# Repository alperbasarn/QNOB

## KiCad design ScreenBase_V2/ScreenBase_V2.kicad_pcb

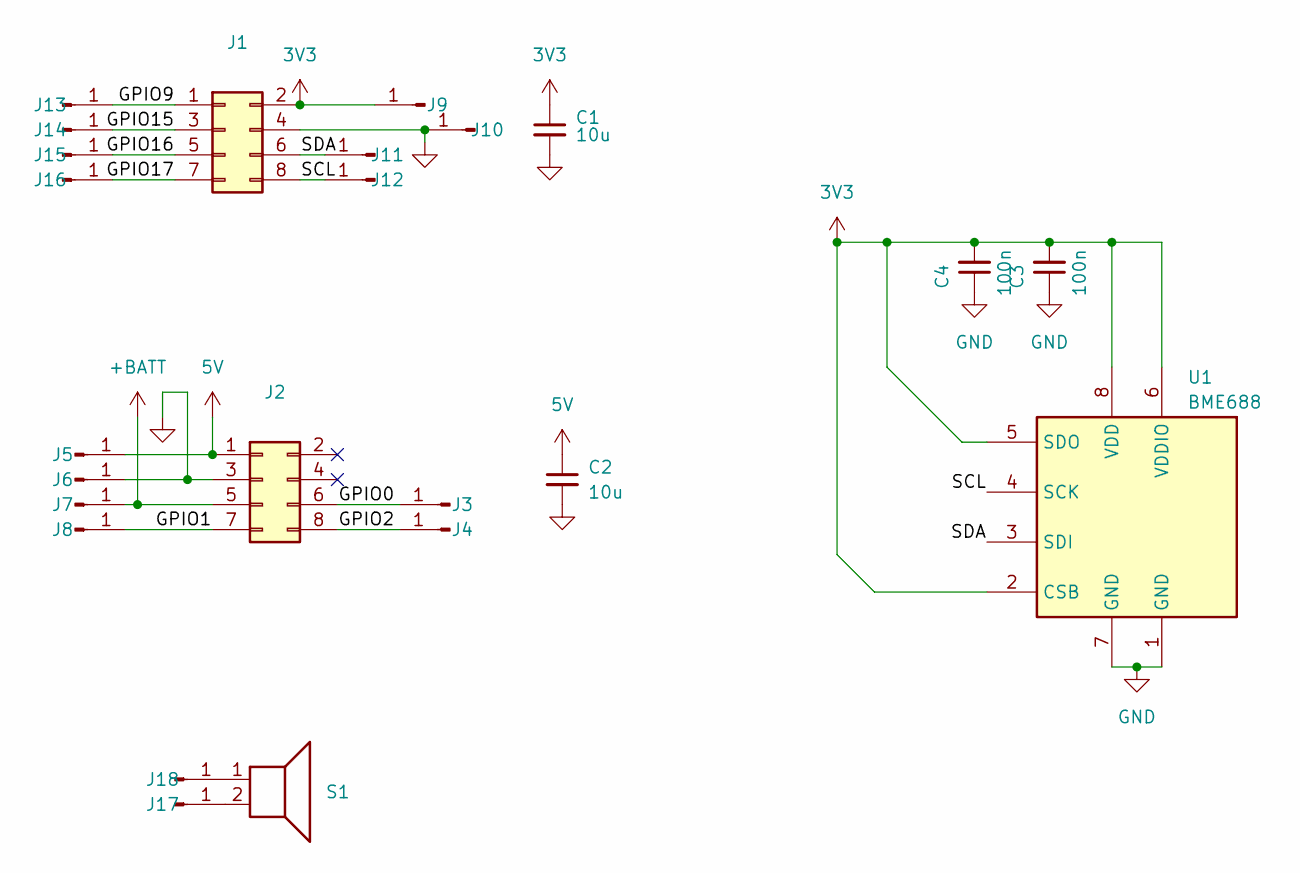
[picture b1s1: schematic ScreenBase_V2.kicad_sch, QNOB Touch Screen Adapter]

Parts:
C1, C2: 10u; C_0805_2012Metric_Pad1.18x1.45mm_HandSolder
C3, C4: 100n; C_0805_2012Metric_Pad1.18x1.45mm_HandSolder
J1, J2: Connector_PinHeader_2.54mm:PinHeader_2x04_P2.54mm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; PinHeader_2x04_P2.54mm_Vertical
J3, J4, J5, J6, J7, J8, J9, J10, J11, J12, J13, J14, J15, J16, J17, J18: Conn_01x01_Pin; SolderWirePad_1x01_SMD_1x2mm
S1: Speaker; speaker_custom
U1: BME688; Bosch_LGA-8_3x3mm_P0.8mm_ClockwisePinNumbering

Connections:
3V3: C1.1, C3.2, C4.2, J1.2, J9.1, U1.2 (CSB), U1.5 (SDO), U1.6 (VDDIO), U1.8 (VDD)
5V: C2.1, J2.1, J5.1
+BATT: J2.5, J7.1
/GPIO0: J2.6, J3.1
/GPIO1: J2.7, J8.1
/GPIO2: J2.8, J4.1
/GPIO9: J1.1, J13.1
/GPIO15: J1.3, J14.1
/GPIO16: J1.5, J15.1
/GPIO17: J1.7, J16.1
/SCL: J1.8, J12.1, U1.4 (SCK)
/SDA: J1.6, J11.1, U1.3 (SDI)
GND: C1.2, C2.2, C3.1, C4.1, J1.4, J2.3, J6.1, J10.1, U1.1 (GND), U1.7 (GND)
unnamed: J17.1, S1.2
unnamed: J18.1, S1.1

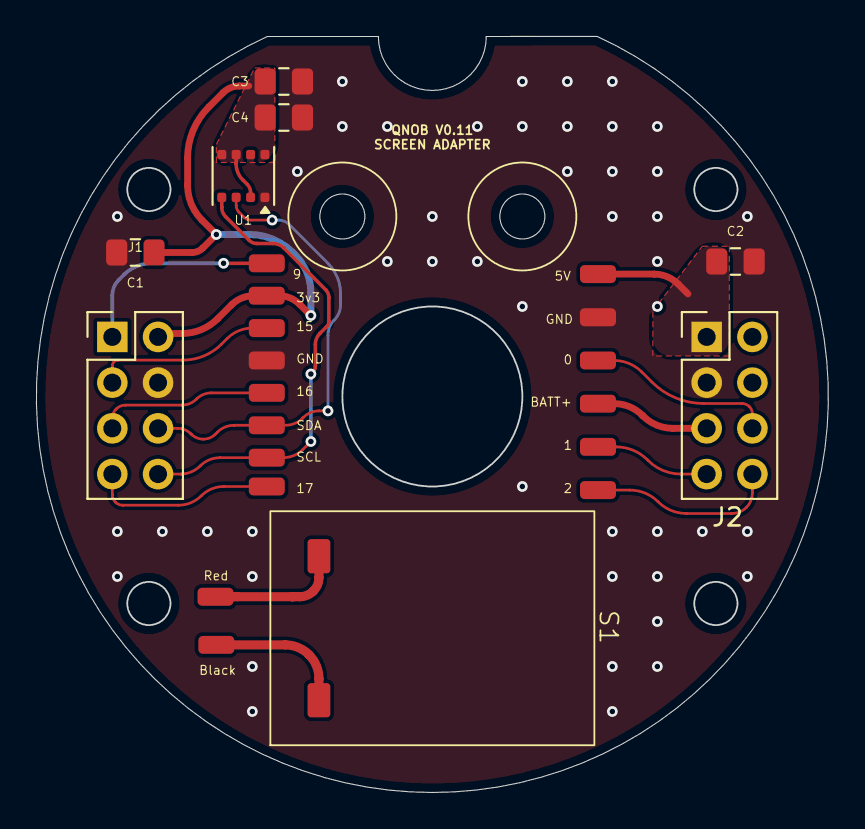
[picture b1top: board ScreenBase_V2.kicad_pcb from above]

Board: 2 copper layers, 44.0 x 42.0 mm, 24 parts (0 on the bottom side), 15 nets.

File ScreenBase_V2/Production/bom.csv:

Designator,Footprint,Quantity,Value,LCSC Part #
"C1, C2",0805,2,10u,
"C3, C4",0805,2,100n,
"J1, J2",PinHeader_2x04_P2.54mm_Vertical,2,Connector_PinHeader_2.54mm:PinHeader_2x04_P2.54mm_Vertical_SMD,
"J10, J11, J12, J13, J14, J15, J16, J17, J18, J3, J4, J5, J6, J7, J8, J9",SolderWirePad_1x01_SMD_1x2mm,16,Conn_01x01_Pin,
S1,speaker_custom,1,Speaker,
U1,Bosch_LGA-8_3x3mm_P0.8mm_ClockwisePinNumbering,1,BME688,

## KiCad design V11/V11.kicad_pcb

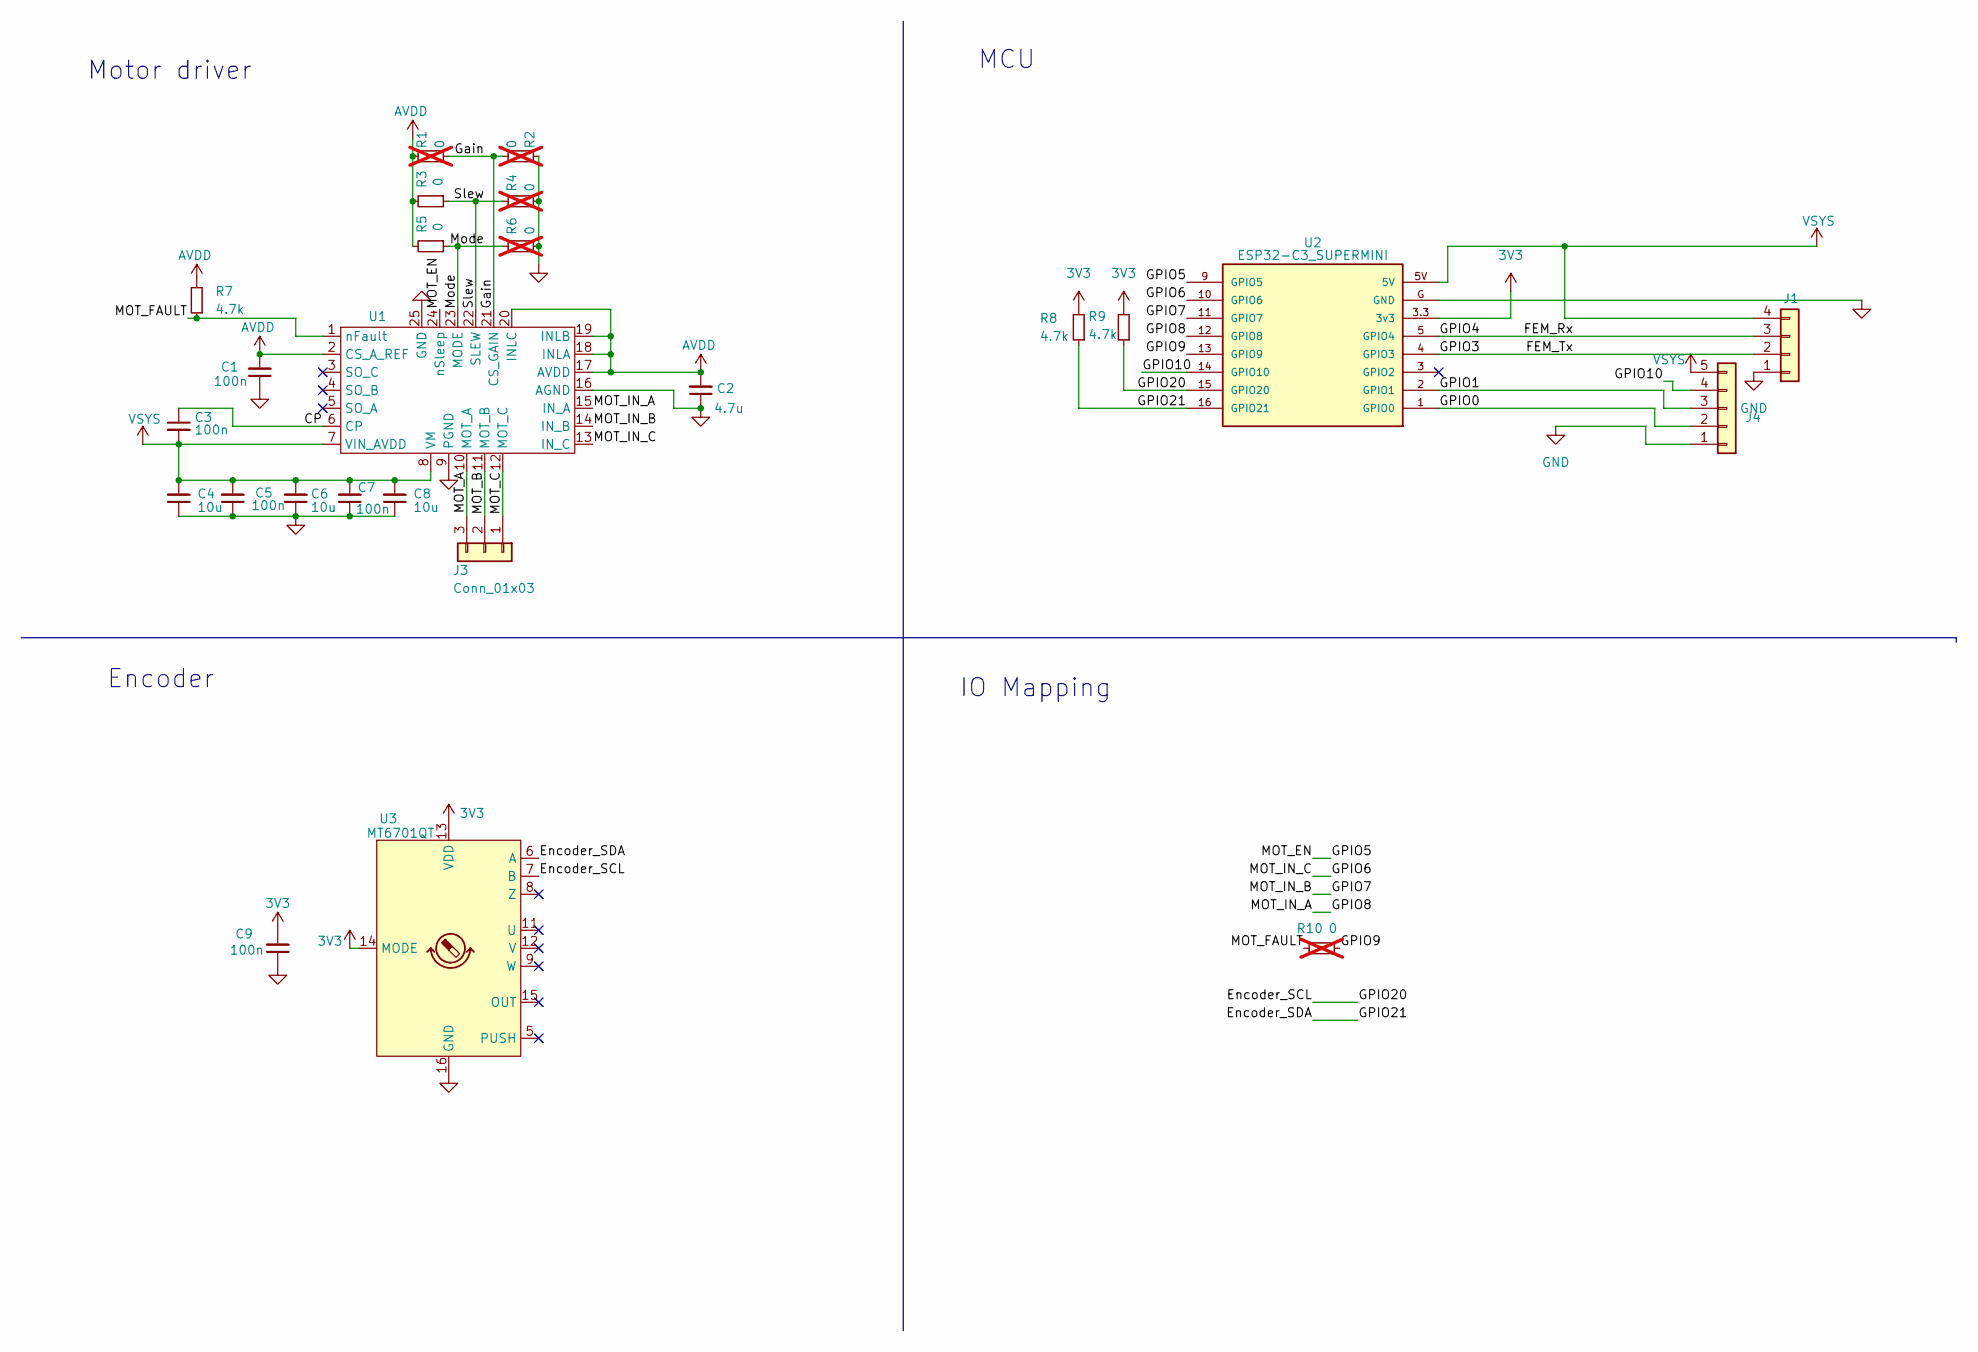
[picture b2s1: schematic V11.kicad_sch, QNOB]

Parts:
C1, C3, C5, C7, C9: 100n; C_0603_1608Metric_Pad1.08x0.95mm_HandSolder
C2: 4.7u; C_0603_1608Metric_Pad1.08x0.95mm_HandSolder
C4, C6, C8: 10u; C_0603_1608Metric_Pad1.08x0.95mm_HandSolder
J1: Conn_01x04; Molex_PicoBlade_53048-0410_1x04_P1.25mm_Horizontal
J3: Conn_01x03; Molex_PicoBlade_53048-0310_1x03_P1.25mm_Horizontal
J4: Conn_01x05; PinHeader_1x05_P2.54mm_Vertical
R1, R2, R4, R6, R10: 0; R_0603_1608Metric_Pad0.98x0.95mm_HandSolder; not fitted
R3, R5: 0; R_0603_1608Metric_Pad0.98x0.95mm_HandSolder
R7, R8, R9: 4.7k; R_0603_1608Metric_Pad0.98x0.95mm_HandSolder
U1: IC_DRV8311HRRWR
U2: ESP32-C3_SUPERMINI; MODULE_ESP32-C3_SUPERMINI
U3: MT6701QT; QFN-16-1EP_3x3mm_P0.5mm_EP1.7x1.7mm

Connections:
3V3: C9.2, R8.2, R9.2, U2.3.3 (3v3), U3.13 (VDD), U3.14 (MODE); also elsewhere on the board
/CP: C3.1, U1.6 (CP)
/CS_A: U1.5 (SO_A)
/CS_B: U1.4 (SO_B)
/CS_C: U1.3 (SO_C)
/Encoder_SCL: R9.1, U2.15 (GPIO20), U3.7 (B)
/Encoder_SDA: R8.1, U2.16 (GPIO21), U3.6 (A)
/FEM_Rx: J1.3, U2.5 (GPIO4)
/FEM_Tx: J1.2, U2.4 (GPIO3)
/GPIO0: J4.2, U2.1 (GPIO0)
/GPIO1: J4.3, U2.2 (GPIO1)
/GPIO5: U1.24 (nSleep), U2.9 (GPIO5)
/GPIO6: U1.13 (IN_C), U2.10 (GPIO6)
/GPIO7: U1.14 (IN_B), U2.11 (GPIO7)
/GPIO8: U1.15 (IN_A), U2.12 (GPIO8)
/GPIO9: R10.1, U2.13 (GPIO9)
/GPIO10: J4.4, U2.14 (GPIO10)
/Gain: R1.1, R2.1, U1.21 (CS_GAIN)
/MOT_A: J3.3, U1.10 (MOT_A)
/MOT_B: J3.2, U1.11 (MOT_B)
/MOT_C: J3.1, U1.12 (MOT_C)
/MOT_FAULT: R7.1, R10.2, U1.1 (nFault)
/Mode: R5.1, R6.2, U1.23 (MODE)
/Slew: R3.1, R4.2, U1.22 (SLEW)
AVDD: C1.2, C2.2, R1.2, R3.2, R5.2, R7.2, U1.2 (CS_A_REF), U1.17 (AVDD), U1.18 (INLA), U1.19 (INLB), U1.20 (INLC)
GND: C1.1, C2.1, C4.1, C5.1, C6.1, C7.1, C8.1, C9.1, J1.1, J4.1, R2.2, R4.1, R6.1, U1.9 (PGND), U1.16 (AGND), U1.25 (GND), U2.G (GND), U3.16 (GND), U3.17 (GND); also elsewhere on the board
VSYS: C3.2, C4.2, C5.2, C6.2, C7.2, C8.2, J1.4, J4.5, U1.7 (VIN_AVDD), U1.8 (VM), U2.5V; also elsewhere on the board

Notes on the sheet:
Encoder
Motor driver
IO Mapping
MCU

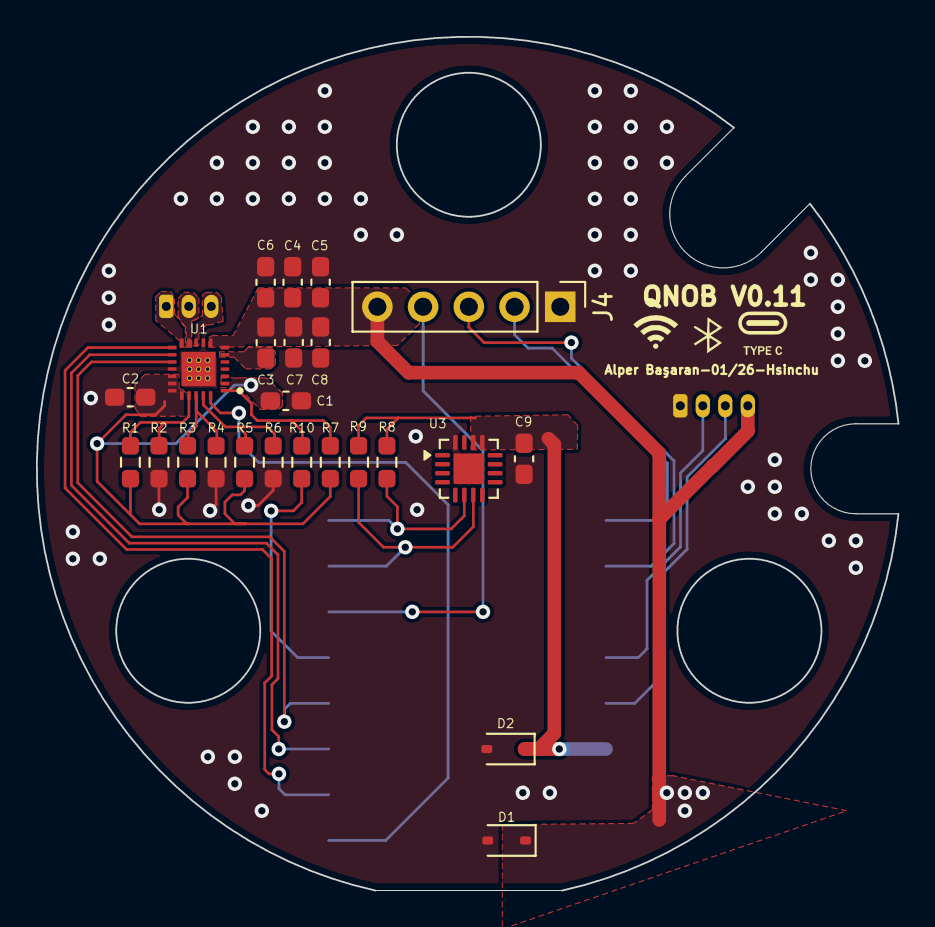
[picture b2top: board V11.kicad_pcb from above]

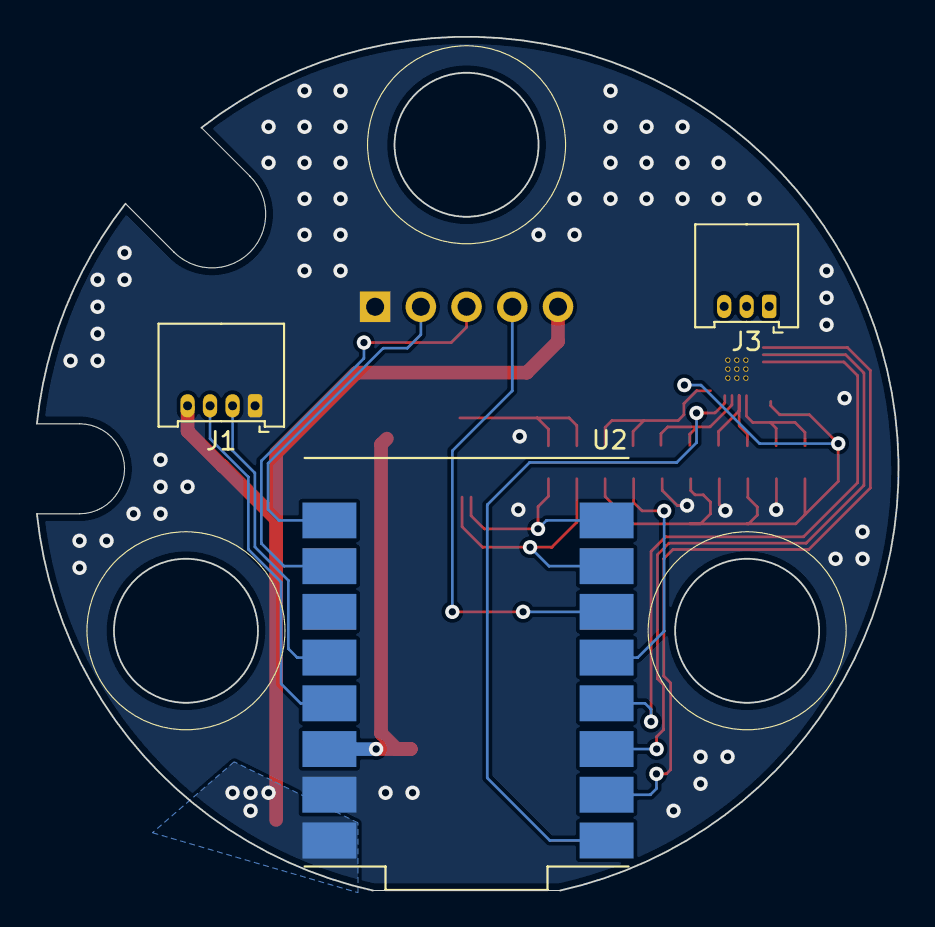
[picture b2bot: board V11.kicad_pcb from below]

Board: 2 copper layers, 47.9 x 47.4 mm, 27 parts (3 on the bottom side), 24 nets.

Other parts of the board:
D1, D2: ESD5Zxx; D_SOD-323

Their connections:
3V3: D2.1 (K); also elsewhere on the board
GND: D1.2 (A), D2.2 (A); also elsewhere on the board
VSYS: D1.1 (K); also elsewhere on the board

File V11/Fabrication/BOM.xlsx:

Comment | Designator | Footprint | JLCPCB Part #（optional）
100n | C1,C3,C5,C7,C9 | 603 | C14663
4.7u | C2 | 603 | C19666
10u | C4,C6,C8 | 603 | C96446
0 | R3,R5 | 603 | C21189
4.7k | R7,R8,R9 | 603 | C23162
DRV8311HRWR | U1 | WQFN-24(3x3) | C5218862
MT6701QT | U3 | QFN-16-1EP_3x3mm_P0.5mm_EP1.7x1.7mm | C2913974

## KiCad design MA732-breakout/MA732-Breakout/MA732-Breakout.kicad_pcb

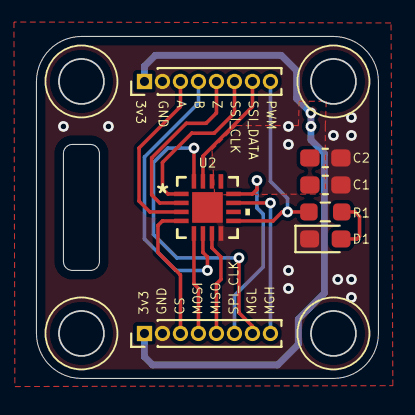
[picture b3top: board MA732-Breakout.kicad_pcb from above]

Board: 2 copper layers, 19.0 x 19.0 mm, 7 parts (0 on the bottom side), 15 nets.

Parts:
C1: 10u; C_0603_1608Metric_Pad1.08x0.95mm_HandSolder
C2: 100n; C_0603_1608Metric_Pad1.08x0.95mm_HandSolder
D1: white; LED_0603_1608Metric_Pad1.05x0.95mm_HandSolder
J1, J2: Conn_01x08_Pin; PinHeader_1x08_P1.00mm_Vertical
R1: 1k; R_0603_1608Metric_Pad0.98x0.95mm_HandSolder
U2: MA732GQ-Z; QFN-16_MA732

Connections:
3v3: C1.2, C2.2, J1.1, J2.1, U2.13 (VDD)
/A: J2.5, U2.2 (A)
/B: J2.4, U2.6 (B)
/CS: J1.4, U2.5 (CS)
/MGH: J1.7, U2.16 (MGH)
/MGL: J1.8, U2.11 (MGL)
/MISO: J1.5, U2.7 (MISO)
/MOSI: J1.3, U2.4 (MOSI)
/PWM: J2.8, R1.1, U2.9 (PWM)
/SPI_CLK: J1.6, U2.12 (SCLK)
/SSI_CLK: J2.7, U2.15 (SSCK)
/SSI_Data: J2.6, U2.1 (SSD)
/Z: J2.3, U2.3 (Z)
GND: C1.1, C2.1, D1.1 (K), J1.2, J2.2, U2.8 (GND), U2.17 (PAD)
unnamed: D1.2 (A), R1.2

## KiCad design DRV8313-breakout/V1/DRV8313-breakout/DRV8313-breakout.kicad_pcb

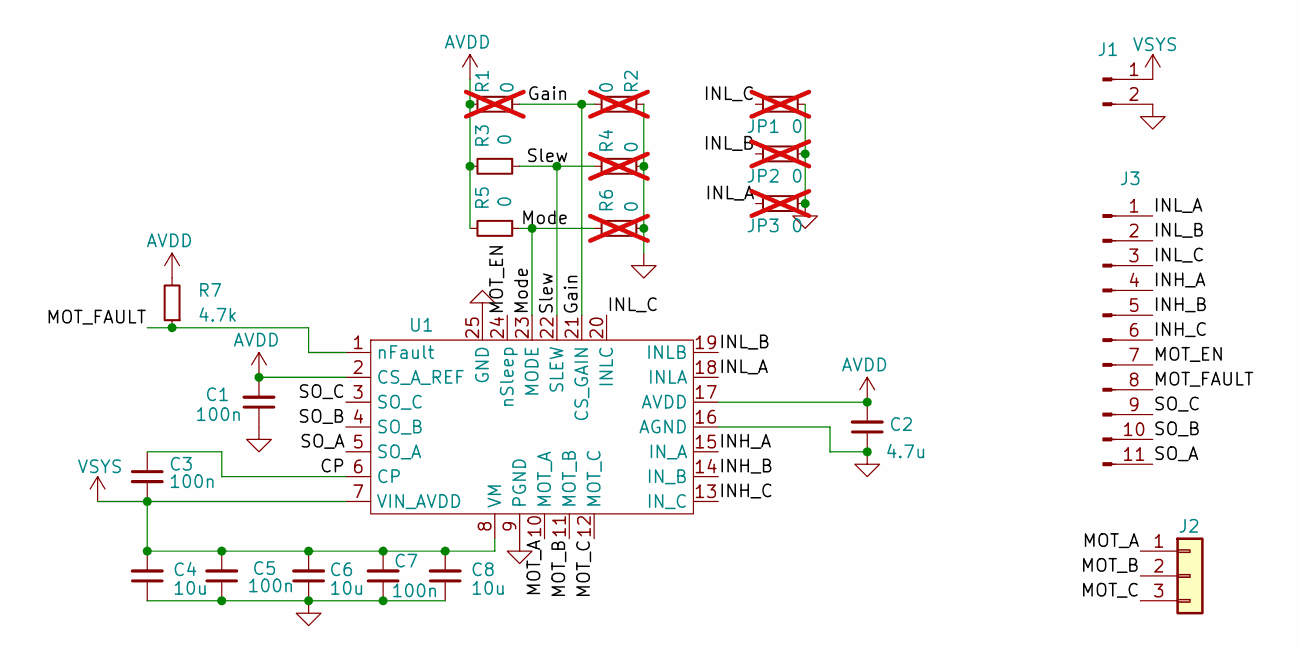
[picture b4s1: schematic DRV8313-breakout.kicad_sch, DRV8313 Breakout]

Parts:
C1, C3, C5, C7: 100n; C_0603_1608Metric_Pad1.08x0.95mm_HandSolder
C2: 4.7u; C_0603_1608Metric_Pad1.08x0.95mm_HandSolder
C4, C6, C8: 10u; C_0603_1608Metric_Pad1.08x0.95mm_HandSolder
J1: Conn_01x02_Pin; Molex_PicoBlade_53048-0210_1x02_P1.25mm_Horizontal
J2: Conn_01x03; Molex_PicoBlade_53048-0310_1x03_P1.25mm_Horizontal
J3: Conn_01x11_Pin; Molex_PicoBlade_53048-1110_1x11_P1.25mm_Horizontal
JP1, JP2, JP3: 0; R_0603_1608Metric_Pad0.98x0.95mm_HandSolder; not fitted
R1, R2, R4, R6: 0; R_0603_1608Metric_Pad0.98x0.95mm_HandSolder; not fitted
R3, R5: 0; R_0603_1608Metric_Pad0.98x0.95mm_HandSolder
R7: 4.7k; R_0603_1608Metric_Pad0.98x0.95mm_HandSolder
U1: IC_DRV8311HRRWR

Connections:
/CP: C3.1, U1.6 (CP)
/Gain: R1.1, R2.1, U1.21 (CS_GAIN)
/INH_A: J3.4, U1.15 (IN_A)
/INH_B: J3.5, U1.14 (IN_B)
/INH_C: J3.6, U1.13 (IN_C)
/INL_A: J3.1, JP3.1, U1.18 (INLA)
/INL_B: J3.2, JP2.1, U1.19 (INLB)
/INL_C: J3.3, JP1.1, U1.20 (INLC)
/MOT_A: J2.1, U1.10 (MOT_A)
/MOT_B: J2.2, U1.11 (MOT_B)
/MOT_C: J2.3, U1.12 (MOT_C)
/MOT_EN: J3.7, U1.24 (nSleep)
/MOT_FAULT: J3.8, R7.1, U1.1 (nFault)
/Mode: R5.1, R6.2, U1.23 (MODE)
/SO_A: J3.11, U1.5 (SO_A)
/SO_B: J3.10, U1.4 (SO_B)
/SO_C: J3.9, U1.3 (SO_C)
/Slew: R3.1, R4.2, U1.22 (SLEW)
AVDD: C1.2, C2.2, R1.2, R3.2, R5.2, R7.2, U1.2 (CS_A_REF), U1.17 (AVDD)
GND: C1.1, C2.1, C4.1, C5.1, C6.1, C7.1, C8.1, J1.2, JP1.2, JP2.2, JP3.2, R2.2, R4.1, R6.1, U1.9 (PGND), U1.16 (AGND), U1.25 (GND)
VSYS: C3.2, C4.2, C5.2, C6.2, C7.2, C8.2, J1.1, U1.7 (VIN_AVDD), U1.8 (VM)

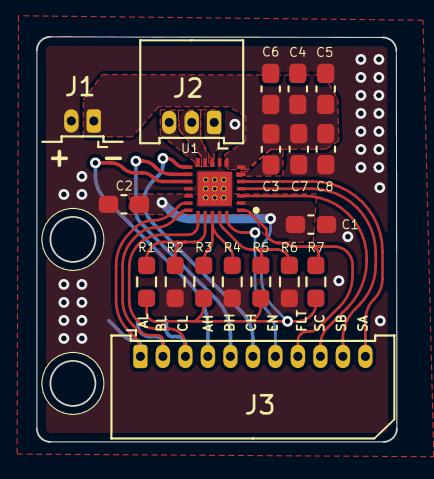
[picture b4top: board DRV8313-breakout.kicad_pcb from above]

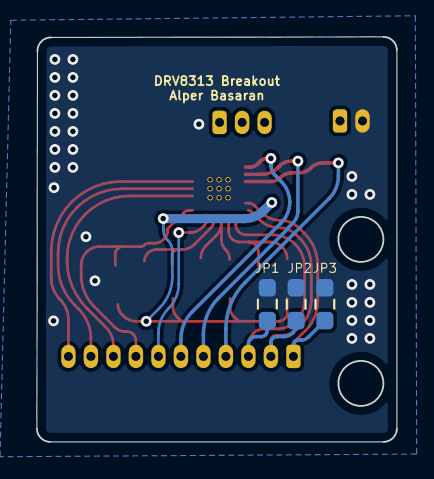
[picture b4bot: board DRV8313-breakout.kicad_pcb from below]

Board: 2 copper layers, 20.0 x 22.5 mm, 22 parts (3 on the bottom side), 21 nets.

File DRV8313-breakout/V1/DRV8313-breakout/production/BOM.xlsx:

Comment | Designator | Footprint | JLCPCB Part #（optional）
100n | C1,C3,C5,C7,C9 | 603 | C14663
4.7u | C2 | 603 | C19666
10u | C4,C6,C8 | 603 | C96446
0 | R3,R5 | 603 | C21189
4.7k | R7 | 603 | C23162
DRV8311HRWR | U1 | WQFN-24(3x3) | C5218862

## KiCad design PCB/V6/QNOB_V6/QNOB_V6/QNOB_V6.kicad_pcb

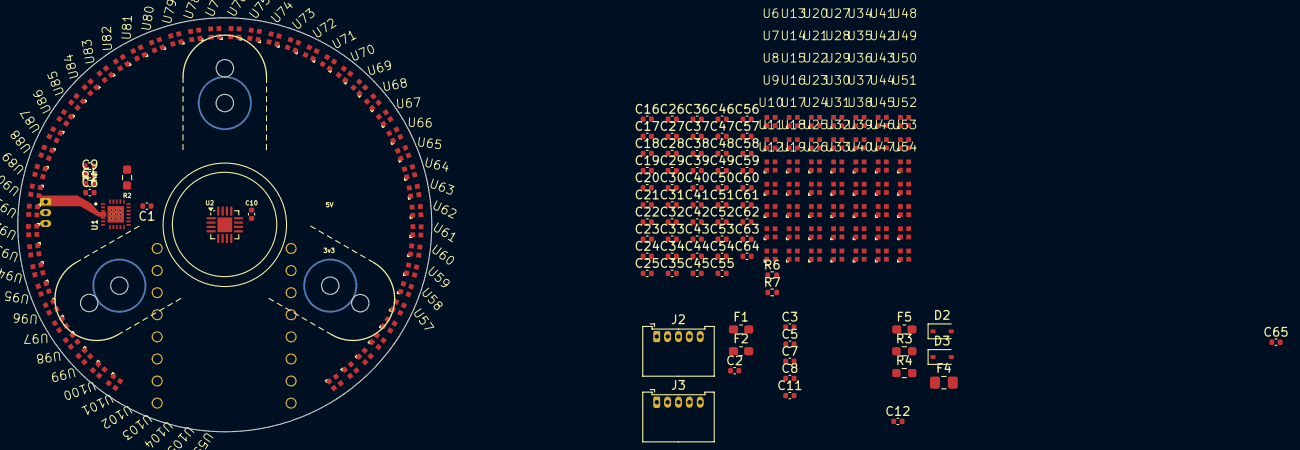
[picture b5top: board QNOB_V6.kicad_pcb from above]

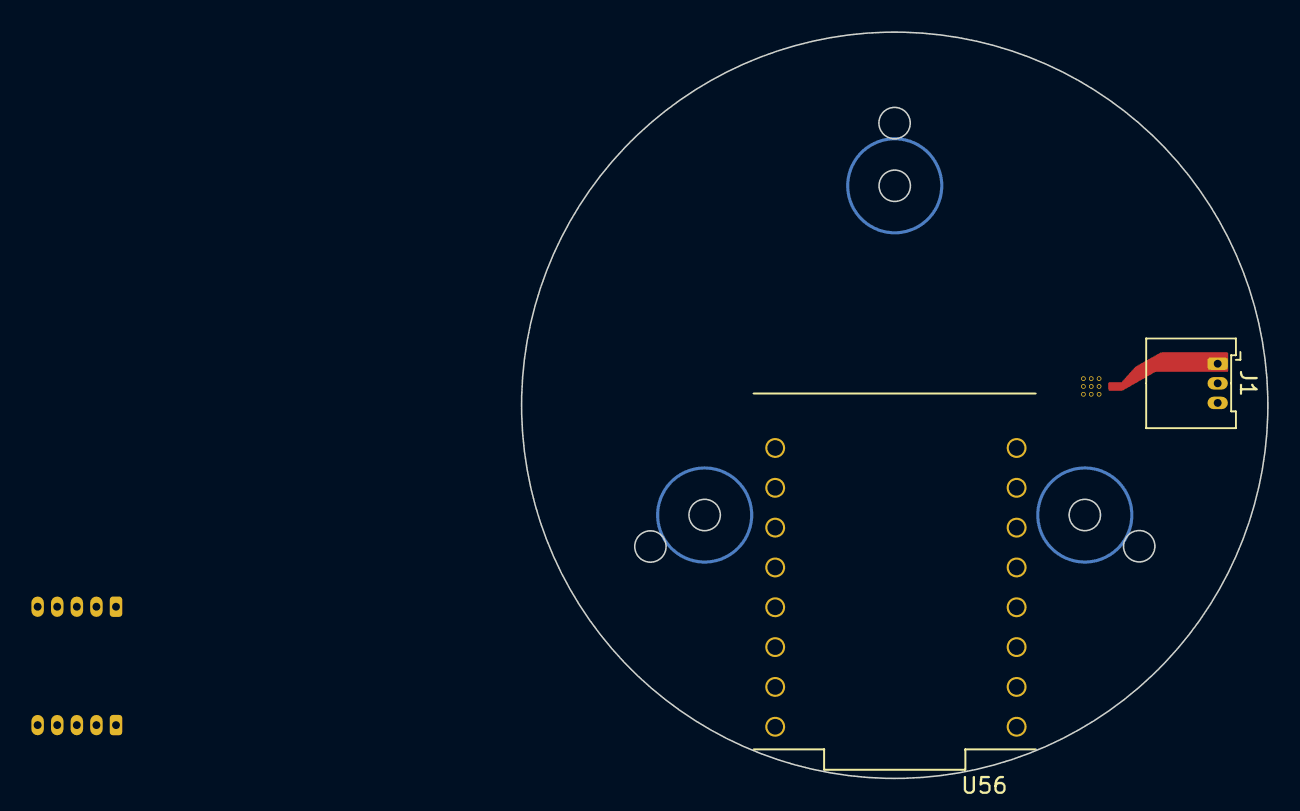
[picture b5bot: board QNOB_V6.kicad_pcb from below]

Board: 2 copper layers, 47.6 x 47.6 mm, 179 parts (2 on the bottom side), 70 nets, no tracks yet.

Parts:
C1, C2, C4, C5, C6, C7: 10u; C_0402_1005Metric
C3, C8, C9, C10, C12: 100n; C_0402_1005Metric
C11: 4.7u; C_0402_1005Metric
C16, C17, C18, C19, C20, C21, C22, C23, C24, C25, C26, C27, C28, C29, C30, C31, C32, C33, C34, C35, C36, C37, C38, C39, C40, C41, C42, C43, C44, C45, C46, C47, C48, C49, C50, C51, C52, C53, C54, C55, C56, C57, C58, C59, C60, C61, C62, C63, C64, C65: 100n 10V; C_0402_1005Metric
D2, D3: ESD5Zxx; D_SOD-323
F1, F2, F5: 500m; Fuse_0603_1608Metric_Pad1.05x0.95mm_HandSolder
F4: 1A; Fuse_0805_2012Metric_Pad1.15x1.40mm_HandSolder
J1: Conn_01x03; Molex_PicoBlade_53048-0310_1x03_P1.25mm_Horizontal
J2, J3: Conn_01x05; Molex_PicoBlade_53048-0510_1x05_P1.25mm_Horizontal
R1: 4.7k; R_0402_1005Metric
R2: 0; R_0603_1608Metric_Pad0.98x0.95mm_HandSolder
R3, R4: 4.7k; R_0603_1608Metric_Pad0.98x0.95mm_HandSolder
R6, R7: 500; R_0402_1005Metric
U1: IC_DRV8311HRRWR
U2: MT6701QT; QFN-16-1EP_3x3mm_P0.5mm_EP1.7x1.7mm
U6, U7, U8, U9, U10, U11, U12, U13, U14, U15, U16, U17, U18, U19, U20, U21, U22, U23, U24, U25, U26, U27, U28, U29, U30, U31, U32, U33, U34, U35, U36, U37, U38, U39, U40, U41, U42, U43, U44, U45, U46, U47, U48, U49, U50, U51, U52, U53, U54, U55, U57, U58, U59, U60, U61, U62, U63, U64, U65, U66, U67, U68, U69, U70, U71, U72, U73, U74, U75, U76, U77, U78, U79, U80, U81, U82, U83, U84, U85, U86, U87, U88, U89, U90, U91, U92, U93, U94, U95, U96, U97, U98, U99, U100, U101, U102, U103, U104, U105: SK6805-EC15
U56: ESP32-C3_SUPERMINI; MODULE_ESP32-C3_SUPERMINI

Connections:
3.3V: F5.1, U56.3.3 (3V3)
3.3V_Protected: C12.2, D3.1 (K), F5.2, R3.2, R4.2, U2.13 (VDD), U2.14 (MODE)
5V: C1.2, C2.2, F1.1, F2.1, F4.1, U56.5V
5V_Protected: C4.2, C5.2, C6.1, C7.2, C8.1, C9.2, C10.2, C16.2, C17.2, C18.2, C19.2, C20.2, C21.2, C22.2, C23.2, C24.2, C25.2, C26.2, C27.2, C28.2, C29.2, C30.2, C31.2, C32.2, C33.2, C34.2, C35.2, C36.2, C37.2, C38.2, C39.2, C40.2, C41.2, C42.2, C43.2, C44.2, C45.2, C46.2, C47.2, C48.2, C49.2, C50.2, C51.2, C52.2, C53.2, C54.2, C55.2, C56.2, C57.2, C58.2, C59.2, C60.2, C61.2, C62.2, C63.2, C64.2, C65.2, D2.1 (K), F4.2, U1.7 (VIN_AVDD), U1.8 (VM), U6.2 (Vin), U7.2 (Vin), U8.2 (Vin), U9.2 (Vin), U10.2 (Vin), U11.2 (Vin), U12.2 (Vin), U13.2 (Vin), U14.2 (Vin), U15.2 (Vin), U16.2 (Vin), U17.2 (Vin), U18.2 (Vin), U19.2 (Vin), U20.2 (Vin), U21.2 (Vin), U22.2 (Vin), U23.2 (Vin), U24.2 (Vin), U25.2 (Vin), U26.2 (Vin), U27.2 (Vin), U28.2 (Vin), U29.2 (Vin), U30.2 (Vin), U31.2 (Vin), U32.2 (Vin), U33.2 (Vin), U34.2 (Vin), U35.2 (Vin), U36.2 (Vin), U37.2 (Vin), U38.2 (Vin), U39.2 (Vin), U40.2 (Vin), U41.2 (Vin), U42.2 (Vin), U43.2 (Vin), U44.2 (Vin), U45.2 (Vin), U46.2 (Vin), U47.2 (Vin), U48.2 (Vin), U49.2 (Vin), U50.2 (Vin), U51.2 (Vin), U52.2 (Vin), U53.2 (Vin), U54.2 (Vin), U55.2 (Vin), U57.2 (Vin), U58.2 (Vin), U59.2 (Vin), U60.2 (Vin), U61.2 (Vin), U62.2 (Vin), U63.2 (Vin), U64.2 (Vin), U65.2 (Vin), U66.2 (Vin), U67.2 (Vin), U68.2 (Vin), U69.2 (Vin), U70.2 (Vin), U71.2 (Vin), U72.2 (Vin), U73.2 (Vin), U74.2 (Vin), U75.2 (Vin), U76.2 (Vin), U77.2 (Vin), U78.2 (Vin), U79.2 (Vin), U80.2 (Vin), U81.2 (Vin), U82.2 (Vin), U83.2 (Vin), U84.2 (Vin), U85.2 (Vin), U86.2 (Vin), U87.2 (Vin), U88.2 (Vin), U89.2 (Vin), U90.2 (Vin), U91.2 (Vin), U92.2 (Vin), U93.2 (Vin), U94.2 (Vin), U95.2 (Vin), U96.2 (Vin), U97.2 (Vin), U98.2 (Vin), U99.2 (Vin), U100.2 (Vin), U101.2 (Vin), U102.2 (Vin), U103.2 (Vin), U104.2 (Vin), U105.2 (Vin)
/GPIO3: J3.3, U56.4 (GPIO4)
/GPIO4: J3.2, U56.3 (GPIO3)
/GPIO5: U1.24 (nSleep), U56.5 (GPIO5)
/GPIO20: J2.4, R3.1, U2.7 (B)
/GPIO21: J2.3, R4.1, U2.6 (A)
/Motor drive/CP: C6.2, C8.2, U1.6 (CP)
/Motor drive/MOT_A: J1.1, U1.10 (MOT_A)
/Motor drive/MOT_B: J1.2, U1.11 (MOT_B)
/Motor drive/MOT_C: J1.3, U1.12 (MOT_C)
GND: C1.1, C2.1, C3.1, C4.1, C5.1, C7.1, C9.1, C10.1, C11.1, C12.1, C16.1, C17.1, C18.1, C19.1, C20.1, C21.1, C22.1, C23.1, C24.1, C25.1, C26.1, C27.1, C28.1, C29.1, C30.1, C31.1, C32.1, C33.1, C34.1, C35.1, C36.1, C37.1, C38.1, C39.1, C40.1, C41.1, C42.1, C43.1, C44.1, C45.1, C46.1, C47.1, C48.1, C49.1, C50.1, C51.1, C52.1, C53.1, C54.1, C55.1, C56.1, C57.1, C58.1, C59.1, C60.1, C61.1, C62.1, C63.1, C64.1, C65.1, D2.2 (A), D3.2 (A), J2.5, J3.1, U1.9 (PGND), U1.16 (AGND), U1.25 (GND), U2.16 (GND), U2.17 (GND), U6.4 (GND), U7.4 (GND), U8.4 (GND), U9.4 (GND), U10.4 (GND), U11.4 (GND), U12.4 (GND), U13.4 (GND), U14.4 (GND), U15.4 (GND), U16.4 (GND), U17.4 (GND), U18.4 (GND), U19.4 (GND), U20.4 (GND), U21.4 (GND), U22.4 (GND), U23.4 (GND), U24.4 (GND), U25.4 (GND), U26.4 (GND), U27.4 (GND), U28.4 (GND), U29.4 (GND), U30.4 (GND), U31.4 (GND), U32.4 (GND), U33.4 (GND), U34.4 (GND), U35.4 (GND), U36.4 (GND), U37.4 (GND), U38.4 (GND), U39.4 (GND), U40.4 (GND), U41.4 (GND), U42.4 (GND), U43.4 (GND), U44.4 (GND), U45.4 (GND), U46.4 (GND), U47.4 (GND), U48.4 (GND), U49.4 (GND), U50.4 (GND), U51.4 (GND), U52.4 (GND), U53.4 (GND), U54.4 (GND), U55.4 (GND), U56.G (GND), U57.4 (GND), U58.4 (GND), U59.4 (GND), U60.4 (GND), U61.4 (GND), U62.4 (GND), U63.4 (GND), U64.4 (GND), U65.4 (GND), U66.4 (GND), U67.4 (GND), U68.4 (GND), U69.4 (GND), U70.4 (GND), U71.4 (GND), U72.4 (GND), U73.4 (GND), U74.4 (GND), U75.4 (GND), U76.4 (GND), U77.4 (GND), U78.4 (GND), U79.4 (GND), U80.4 (GND), U81.4 (GND), U82.4 (GND), U83.4 (GND), U84.4 (GND), U85.4 (GND), U86.4 (GND), U87.4 (GND), U88.4 (GND), U89.4 (GND), U90.4 (GND), U91.4 (GND), U92.4 (GND), U93.4 (GND), U94.4 (GND), U95.4 (GND), U96.4 (GND), U97.4 (GND), U98.4 (GND), U99.4 (GND), U100.4 (GND), U101.4 (GND), U102.4 (GND), U103.4 (GND), U104.4 (GND), U105.4 (GND)
unnamed: F1.2, J2.1
unnamed: F2.2, J3.5
unnamed: C3.2, C11.2, R1.2, R2.2, U1.2 (CS_A_REF), U1.17 (AVDD), U1.18 (INLA), U1.19 (INLB), U1.20 (INLC), U1.22 (SLEW), U1.23 (MODE)
unnamed: R2.1, U1.21 (CS_GAIN)
unnamed: R1.1, U1.1 (nFault)
unnamed: R6.1, U10.1 (DIn)
unnamed: U10.3 (Dout), U15.1 (DIn)
unnamed: U6.3 (Dout), U11.1 (DIn)
unnamed: U11.3 (Dout), U16.1 (DIn)
unnamed: U7.3 (Dout), U12.1 (DIn)
unnamed: U12.3 (Dout), U17.1 (DIn)
unnamed: U8.3 (Dout), U13.1 (DIn)
unnamed: U13.3 (Dout), U18.1 (DIn)
unnamed: U9.3 (Dout), U14.1 (DIn)
unnamed: U14.3 (Dout), U19.1 (DIn)
unnamed: U15.3 (Dout), U20.1 (DIn)
unnamed: U16.3 (Dout), U21.1 (DIn)
unnamed: U17.3 (Dout), U22.1 (DIn)
unnamed: U18.3 (Dout), U23.1 (DIn)
unnamed: U19.3 (Dout), U24.1 (DIn)
unnamed: U20.3 (Dout), U25.1 (DIn)
unnamed: U21.3 (Dout), U26.1 (DIn)
unnamed: U22.3 (Dout), U27.1 (DIn)
unnamed: U23.3 (Dout), U28.1 (DIn)
unnamed: U24.3 (Dout), U29.1 (DIn)
unnamed: U25.3 (Dout), U30.1 (DIn)
unnamed: U26.3 (Dout), U31.1 (DIn)
unnamed: U27.3 (Dout), U32.1 (DIn)
unnamed: U28.3 (Dout), U33.1 (DIn)
unnamed: U29.3 (Dout), U34.1 (DIn)
unnamed: U30.3 (Dout), U35.1 (DIn)
unnamed: U31.3 (Dout), U36.1 (DIn)
unnamed: U32.3 (Dout), U37.1 (DIn)
unnamed: U33.3 (Dout), U38.1 (DIn)
unnamed: U34.3 (Dout), U39.1 (DIn)
unnamed: U35.3 (Dout), U40.1 (DIn)
unnamed: U36.3 (Dout), U41.1 (DIn)
unnamed: U37.3 (Dout), U42.1 (DIn)
unnamed: U38.3 (Dout), U43.1 (DIn)
unnamed: U39.3 (Dout), U44.1 (DIn)
unnamed: U40.3 (Dout), U45.1 (DIn)
unnamed: U41.3 (Dout), U46.1 (DIn)
unnamed: U42.3 (Dout), U47.1 (DIn)
unnamed: U43.3 (Dout), U48.1 (DIn)
unnamed: U44.3 (Dout), U49.1 (DIn)
unnamed: U45.3 (Dout), U50.1 (DIn)
unnamed: U46.3 (Dout), U51.1 (DIn)
unnamed: U47.3 (Dout), U52.1 (DIn)
unnamed: U48.3 (Dout), U53.1 (DIn)
unnamed: U49.3 (Dout), U54.1 (DIn)
unnamed: U50.3 (Dout), U55.1 (DIn), U57.1 (DIn), U58.1 (DIn), U59.1 (DIn), U60.1 (DIn), U61.1 (DIn), U62.1 (DIn), U63.1 (DIn), U64.1 (DIn), U65.1 (DIn), U66.1 (DIn), U67.1 (DIn), U68.1 (DIn), U69.1 (DIn), U70.1 (DIn), U71.1 (DIn), U72.1 (DIn), U73.1 (DIn), U74.1 (DIn), U75.1 (DIn), U76.1 (DIn), U77.1 (DIn), U78.1 (DIn), U79.1 (DIn), U80.1 (DIn), U81.1 (DIn), U82.1 (DIn), U83.1 (DIn), U84.1 (DIn), U85.1 (DIn), U86.1 (DIn), U87.1 (DIn), U88.1 (DIn), U89.1 (DIn), U90.1 (DIn), U91.1 (DIn), U92.1 (DIn), U93.1 (DIn), U94.1 (DIn), U95.1 (DIn), U96.1 (DIn), U97.1 (DIn), U98.1 (DIn), U99.1 (DIn), U100.1 (DIn), U101.1 (DIn), U102.1 (DIn), U103.1 (DIn), U104.1 (DIn), U105.1 (DIn)
unnamed: R7.2, U51.3 (Dout)
unnamed: U6.1 (DIn), U52.3 (Dout)
unnamed: U7.1 (DIn), U53.3 (Dout)
unnamed: U8.1 (DIn), U54.3 (Dout)
unnamed: U9.1 (DIn), U55.3 (Dout), U57.3 (Dout), U58.3 (Dout), U59.3 (Dout), U60.3 (Dout), U61.3 (Dout), U62.3 (Dout), U63.3 (Dout), U64.3 (Dout), U65.3 (Dout), U66.3 (Dout), U67.3 (Dout), U68.3 (Dout), U69.3 (Dout), U70.3 (Dout), U71.3 (Dout), U72.3 (Dout), U73.3 (Dout), U74.3 (Dout), U75.3 (Dout), U76.3 (Dout), U77.3 (Dout), U78.3 (Dout), U79.3 (Dout), U80.3 (Dout), U81.3 (Dout), U82.3 (Dout), U83.3 (Dout), U84.3 (Dout), U85.3 (Dout), U86.3 (Dout), U87.3 (Dout), U88.3 (Dout), U89.3 (Dout), U90.3 (Dout), U91.3 (Dout), U92.3 (Dout), U93.3 (Dout), U94.3 (Dout), U95.3 (Dout), U96.3 (Dout), U97.3 (Dout), U98.3 (Dout), U99.3 (Dout), U100.3 (Dout), U101.3 (Dout), U102.3 (Dout), U103.3 (Dout), U104.3 (Dout), U105.3 (Dout)

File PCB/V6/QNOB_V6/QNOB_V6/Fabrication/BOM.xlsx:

Comment | Designator | Footprint | LCSC Part #（optional）
4.7u | C1 | 603 | C19666
10u | C2 | 603 | C96446
10u | C3 | 603 | C96446
100n | C4 | 603 | C14663
100n | C5 | 603 | C14663
100n | C6 | 603 | C14663
100n | C7 | 603 | C14663
100n/0402 | C8 | 402 | C1525
100n/0402 | C10 | 402 | C1525
100n/0402 | C11 | 402 | C1525
100n/0402 | C12 | 402 | C1525
100n/0402 | C13 | 402 | C1525
100n/0402 | C14 | 402 | C1525
100n/0402 | C15 | 402 | C1525
100n/0402 | C16 | 402 | C1525
100n/0402 | C17 | 402 | C1525
100n/0402 | C18 | 402 | C1525
100n/0402 | C19 | 402 | C1525
100n/0402 | C20 | 402 | C1525
100n/0402 | C21 | 402 | C1525
100n/0402 | C22 | 402 | C1525
100n/0402 | C23 | 402 | C1525
100n/0402 | C24 | 402 | C1525
100n/0402 | C25 | 402 | C1525
100n/0402 | C26 | 402 | C1525
100n/0402 | C27 | 402 | C1525
100n/0402 | C28 | 402 | C1525
100n/0402 | C29 | 402 | C1525
100n/0402 | C30 | 402 | C1525
100n/0402 | C31 | 402 | C1525
100n/0402 | C32 | 402 | C1525
100n/0402 | C33 | 402 | C1525
100n/0402 | C34 | 402 | C1525
100n/0402 | C35 | 402 | C1525
100n/0402 | C36 | 402 | C1525
100n/0402 | C37 | 402 | C1525
100n/0402 | C38 | 402 | C1525
100n/0402 | C39 | 402 | C1525
100n/0402 | C40 | 402 | C1525
100n/0402 | C41 | 402 | C1525
100n/0402 | C42 | 402 | C1525
100n/0402 | C43 | 402 | C1525
100n/0402 | C44 | 402 | C1525
100n/0402 | C45 | 402 | C1525
100n/0402 | C46 | 402 | C1525
100n/0402 | C47 | 402 | C1525
100n/0402 | C48 | 402 | C1525
100n/0402 | C49 | 402 | C1525
100n/0402 | C50 | 402 | C1525
100n/0402 | C51 | 402 | C1525
100n/0402 | C52 | 402 | C1525
100n/0402 | C53 | 402 | C1525
100n/0402 | C54 | 402 | C1525
100n/0402 | C55 | 402 | C1525
100n/0402 | C56 | 402 | C1525
100n/0402 | C57 | 402 | C1525
100n/0402 | C58 | 402 | C1525
100n/0402 | C59 | 402 | C1525
100n/0402 | C62 | 402 | C1525
100n/0402 | C63 | 402 | C1525
10u | C60 | 603 | C96446
10u | C64 | 603 | C96446
100n | C65 | 603 | C14663
10u | C66 | 603 | C96446
10u | C67 | 603 | C96446
10u | C68 | 603 | C96446
100n | C69 | 603 | C14663
D_SOD-323 | D1 | SMT | C344002
D_SOD-323 | D2 | SMT | C344002
500mA | F1 | SMT | C20976
500mA | F2 | SMT | C20785
500mA | F3 | SMT | C20785
500mA | F4 | SMT | C20785
0 | R1 | 603 | C21189
4.7k | R2 | 603 | C23162
4.7k | R3 | 603 | C23162
4.7k | R4 | 603 | C23162
2k | R5 | 402 | C4109
2k | R6 | 402 | C4109
4.7k | R8 | 603 | C23162
DRV8311HRRWR | U2 | WQFN-24(3x3) | C5218862
MT6701CT | U3 | SOP-8 | C2913974
Adressable RGB LED | U4 | 606 | C2890035
Adressable RGB LED | U5 | 606 | C2890035
Adressable RGB LED | U6 | 606 | C2890035
Adressable RGB LED | U7 | 606 | C2890035
Adressable RGB LED | U8 | 606 | C2890035
Adressable RGB LED | U9 | 606 | C2890035
Adressable RGB LED | U10 | 606 | C2890035
Adressable RGB LED | U11 | 606 | C2890035
Adressable RGB LED | U12 | 606 | C2890035
Adressable RGB LED | U13 | 606 | C2890035
Adressable RGB LED | U14 | 606 | C2890035
Adressable RGB LED | U15 | 606 | C2890035
Adressable RGB LED | U16 | 606 | C2890035
Adressable RGB LED | U17 | 606 | C2890035
Adressable RGB LED | U18 | 606 | C2890035
Adressable RGB LED | U19 | 606 | C2890035
Adressable RGB LED | U20 | 606 | C2890035
Adressable RGB LED | U21 | 606 | C2890035
Adressable RGB LED | U22 | 606 | C2890035
Adressable RGB LED | U23 | 606 | C2890035
Adressable RGB LED | U24 | 606 | C2890035
Adressable RGB LED | U25 | 606 | C2890035
Adressable RGB LED | U26 | 606 | C2890035
Adressable RGB LED | U27 | 606 | C2890035
Adressable RGB LED | U28 | 606 | C2890035
Adressable RGB LED | U29 | 606 | C2890035
Adressable RGB LED | U30 | 606 | C2890035
Adressable RGB LED | U31 | 606 | C2890035
Adressable RGB LED | U32 | 606 | C2890035
Adressable RGB LED | U33 | 606 | C2890035
Adressable RGB LED | U34 | 606 | C2890035
Adressable RGB LED | U35 | 606 | C2890035
Adressable RGB LED | U36 | 606 | C2890035
Adressable RGB LED | U37 | 606 | C2890035
Adressable RGB LED | U38 | 606 | C2890035
Adressable RGB LED | U39 | 606 | C2890035
Adressable RGB LED | U40 | 606 | C2890035
Adressable RGB LED | U41 | 606 | C2890035
Adressable RGB LED | U42 | 606 | C2890035
Adressable RGB LED | U43 | 606 | C2890035
Adressable RGB LED | U44 | 606 | C2890035
Adressable RGB LED | U45 | 606 | C2890035
Adressable RGB LED | U46 | 606 | C2890035
Adressable RGB LED | U47 | 606 | C2890035
Adressable RGB LED | U48 | 606 | C2890035
Adressable RGB LED | U49 | 606 | C2890035
Adressable RGB LED | U50 | 606 | C2890035
Adressable RGB LED | U51 | 606 | C2890035
Adressable RGB LED | U52 | 606 | C2890035
Adressable RGB LED | U53 | 606 | C2890035
RTC | U54 | 606 | C26858
Environment sensor | U55 | SMT | C3664478
Lux sensor | U57 | SMT | C511034
32768 crystal | Y1 | 3215-2p | C32346

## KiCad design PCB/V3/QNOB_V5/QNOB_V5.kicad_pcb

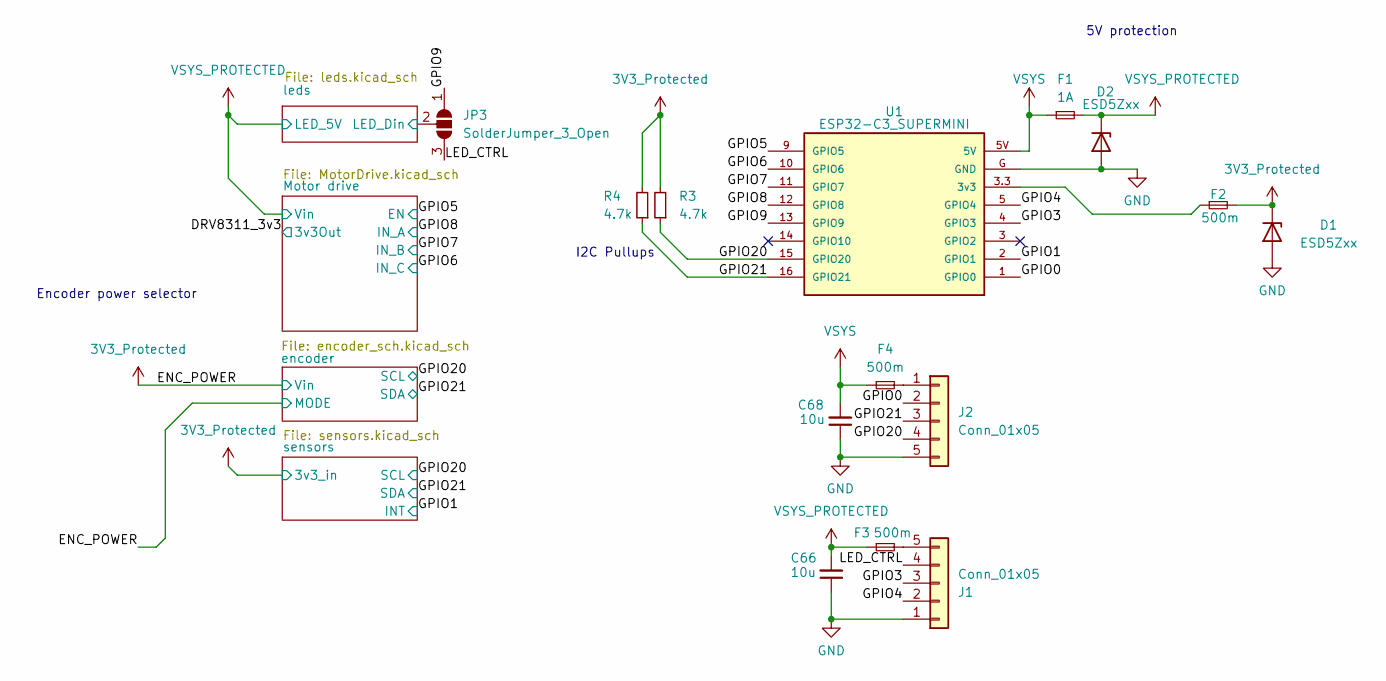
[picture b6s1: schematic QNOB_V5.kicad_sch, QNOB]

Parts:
C66, C68: 10u; CP_EIA-1608-08_AVX-J_Pad1.25x1.05mm_HandSolder
D1, D2: ESD5Zxx; D_SOD-323
F1: 1A; Fuse_0805_2012Metric_Pad1.15x1.40mm_HandSolder
F2, F3, F4: 500m; Fuse_0603_1608Metric_Pad1.05x0.95mm_HandSolder
J1, J2: Conn_01x05; Molex_PicoBlade_53048-0510_1x05_P1.25mm_Horizontal
JP3: SolderJumper_3_Open; SolderJumper-3_P1.3mm_Open_RoundedPad1.0x1.5mm
R3, R4: 4.7k; R_0603_1608Metric_Pad0.98x0.95mm_HandSolder
U1: ESP32-C3_SUPERMINI; MODULE_ESP32-C3_SUPERMINI

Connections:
3V3_Protected: D1.1 (K), F2.2, R3.2, R4.2; also elsewhere on the board
/GPIO0: J2.2, U1.1 (GPIO0)
/GPIO1: U1.2 (GPIO1); also elsewhere on the board
/GPIO3: J1.3, U1.4 (GPIO3)
/GPIO4: J1.2, U1.5 (GPIO4)
/GPIO5: U1.9 (GPIO5); also elsewhere on the board
/GPIO6: U1.10 (GPIO6); also elsewhere on the board
/GPIO7: U1.11 (GPIO7); also elsewhere on the board
/GPIO8: U1.12 (GPIO8); also elsewhere on the board
/GPIO9: JP3.1 (A), U1.13 (GPIO9); also elsewhere on the board
/GPIO20: J2.4, R3.1, U1.15 (GPIO20); also elsewhere on the board
/GPIO21: J2.3, R4.1, U1.16 (GPIO21); also elsewhere on the board
/LED_CTRL: J1.4, JP3.3 (B)
/leds/LED_Din: JP3.2 (C); also elsewhere on the board
GND: C66.1, C68.1, D1.2 (A), D2.2 (A), J1.1, J2.5, U1.G (GND); also elsewhere on the board
unnamed: F3.2, J1.5
unnamed: F4.2, J2.1
unnamed: F2.1, U1.3.3 (3v3)
VSYS: C68.2, F1.1, F4.1, U1.5V
VSYS_PROTECTED: C66.2, D2.1 (K), F1.2, F3.1; also elsewhere on the board

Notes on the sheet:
I2C Pullups
Encoder power selector
5V protection
